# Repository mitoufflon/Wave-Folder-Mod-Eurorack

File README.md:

# Wave-Folder-Mod-Eurorack
Wave Folder from CGS stripboard version

Schematic made with [diylc](https://bancika.github.io/diy-layout-creator/)
and kiCad

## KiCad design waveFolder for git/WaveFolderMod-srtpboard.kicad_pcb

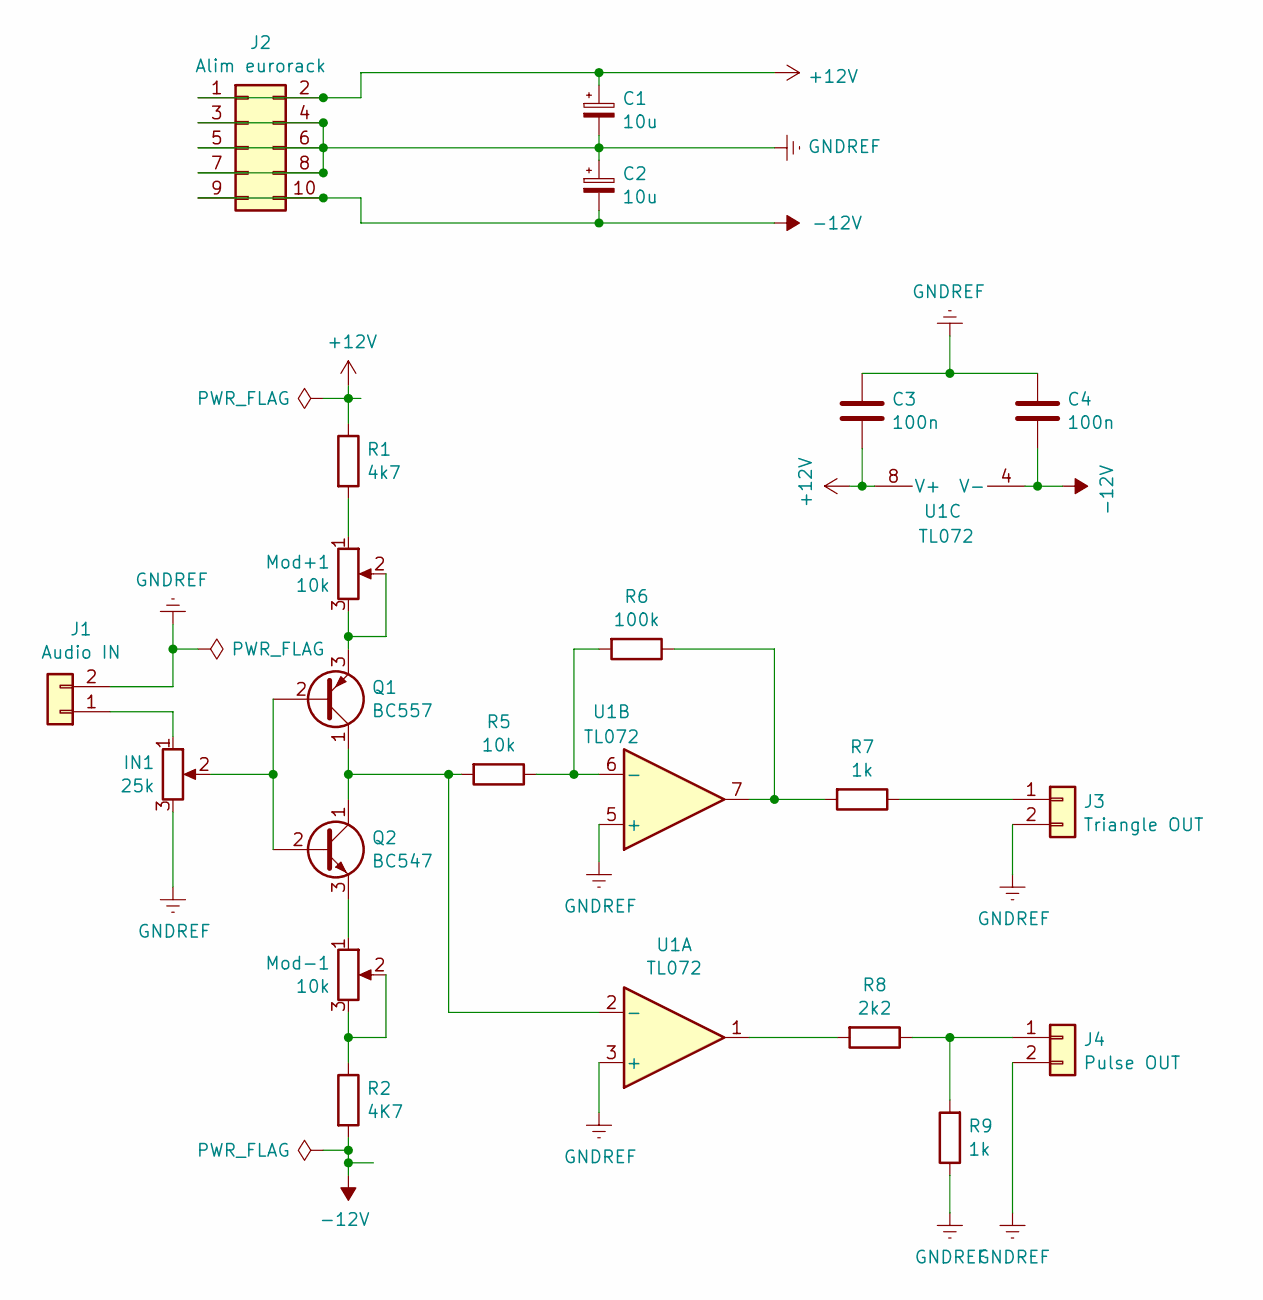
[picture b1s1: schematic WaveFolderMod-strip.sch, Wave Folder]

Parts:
C1, C2: 10u; CP_Radial_D5.0mm_P2.50mm
C3, C4: 100n; C_Rect_L7.0mm_W2.5mm_P5.00mm
IN1: 25k; Potentiometer_Alps_RK09Y11_Single_Horizontal
J1: Audio IN; PinHeader_1x02_P2.54mm_Vertical
J2: Alim eurorack; PinHeader_2x05_P2.54mm_Vertical
J3: Triangle OUT; PinHeader_1x02_P2.54mm_Vertical
J4: Pulse OUT; PinHeader_1x02_P2.54mm_Vertical
Mod+1: 10k; Potentiometer_Alps_RK09Y11_Single_Horizontal
Mod-1: 10k; Potentiometer_Alps_RK09Y11_Single_Horizontal
Q1: BC557; TO-92_Inline
Q2: BC547; TO-92_Inline
R1: 4k7; R_Axial_DIN0207_L6.3mm_D2.5mm_P2.54mm_Vertical
R2: 4K7; R_Axial_DIN0207_L6.3mm_D2.5mm_P2.54mm_Vertical
R5: 10k; R_Axial_DIN0207_L6.3mm_D2.5mm_P7.62mm_Horizontal
R6: 100k; R_Axial_DIN0207_L6.3mm_D2.5mm_P10.16mm_Horizontal
R7: 1k; R_Axial_DIN0207_L6.3mm_D2.5mm_P10.16mm_Horizontal
R8: 2k2; R_Axial_DIN0207_L6.3mm_D2.5mm_P2.54mm_Vertical
R9: 1k; R_Axial_DIN0207_L6.3mm_D2.5mm_P2.54mm_Vertical
U1: TL072; DIP-8_W7.62mm

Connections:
+12V: C1.1, C3.2, J2.1, J2.2, R1.1, U1.8 (V+)
-12V: C2.2, C4.2, J2.9, J2.10, R2.2, U1.4 (V-)
GNDREF: C1.2, C2.1, C3.1, C4.1, IN1.3, J1.2, J2.3, J2.4, J2.5, J2.6, J2.7, J2.8, J3.2, J4.2, R9.1, U1.3 (+), U1.5 (+)
unnamed: IN1.1, J1.1
unnamed: IN1.2, Q1.2 (B), Q2.2 (B)
unnamed: J3.1, R7.1
unnamed: J4.1, R8.1, R9.2
unnamed: Mod+1.1, R1.2
unnamed: Mod+1.2, Mod+1.3, Q1.3 (E)
unnamed: Mod-1.1, Q2.3 (E)
unnamed: Mod-1.2, Mod-1.3, R2.1
unnamed: Q1.1 (C), Q2.1 (C), R5.2, U1.2 (-)
unnamed: R5.1, R6.2, U1.6 (-)
unnamed: R6.1, R7.2, U1.7
unnamed: R8.2, U1.1

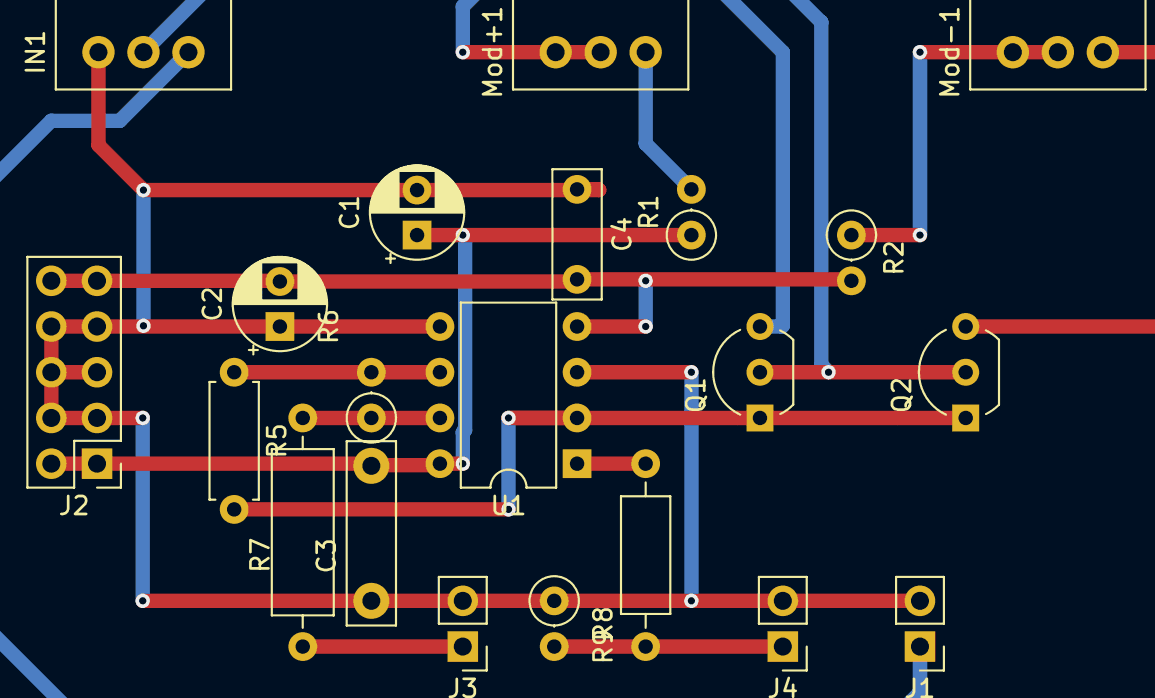
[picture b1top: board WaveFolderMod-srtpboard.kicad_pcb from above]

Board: 2 copper layers, 21 parts (0 on the bottom side), 15 nets.

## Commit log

2020-02-09 Version for stripboard
2020-02-09 Kicad Files
2020-02-11 little fix
2020-02-11 Update README with image
